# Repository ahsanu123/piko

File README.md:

<h1>🐤 piko </h1>
<p>

</p>

<p align="center">CMSIS DAP Probe</p>

### 🧺 Schematic

## Reference

- make new project Piko, picoprobe based on https://github.com/ErichStyger/mcuoneclipse/tree/master/KiCAD/Projects/PicoLink
- wagiminator ch552 daplink https://github.com/wagiminator/CH552-DAPLink
- yapicoprobe https://github.com/rgrr/yapicoprobe/blob/master/doc/hardware.adoc
- mcu on eclipse picolink https://mcuoneclipse.com/2023/04/08/open-source-picolink-raspberry-pi-rp2040-cmsis-dap-debug-probe/

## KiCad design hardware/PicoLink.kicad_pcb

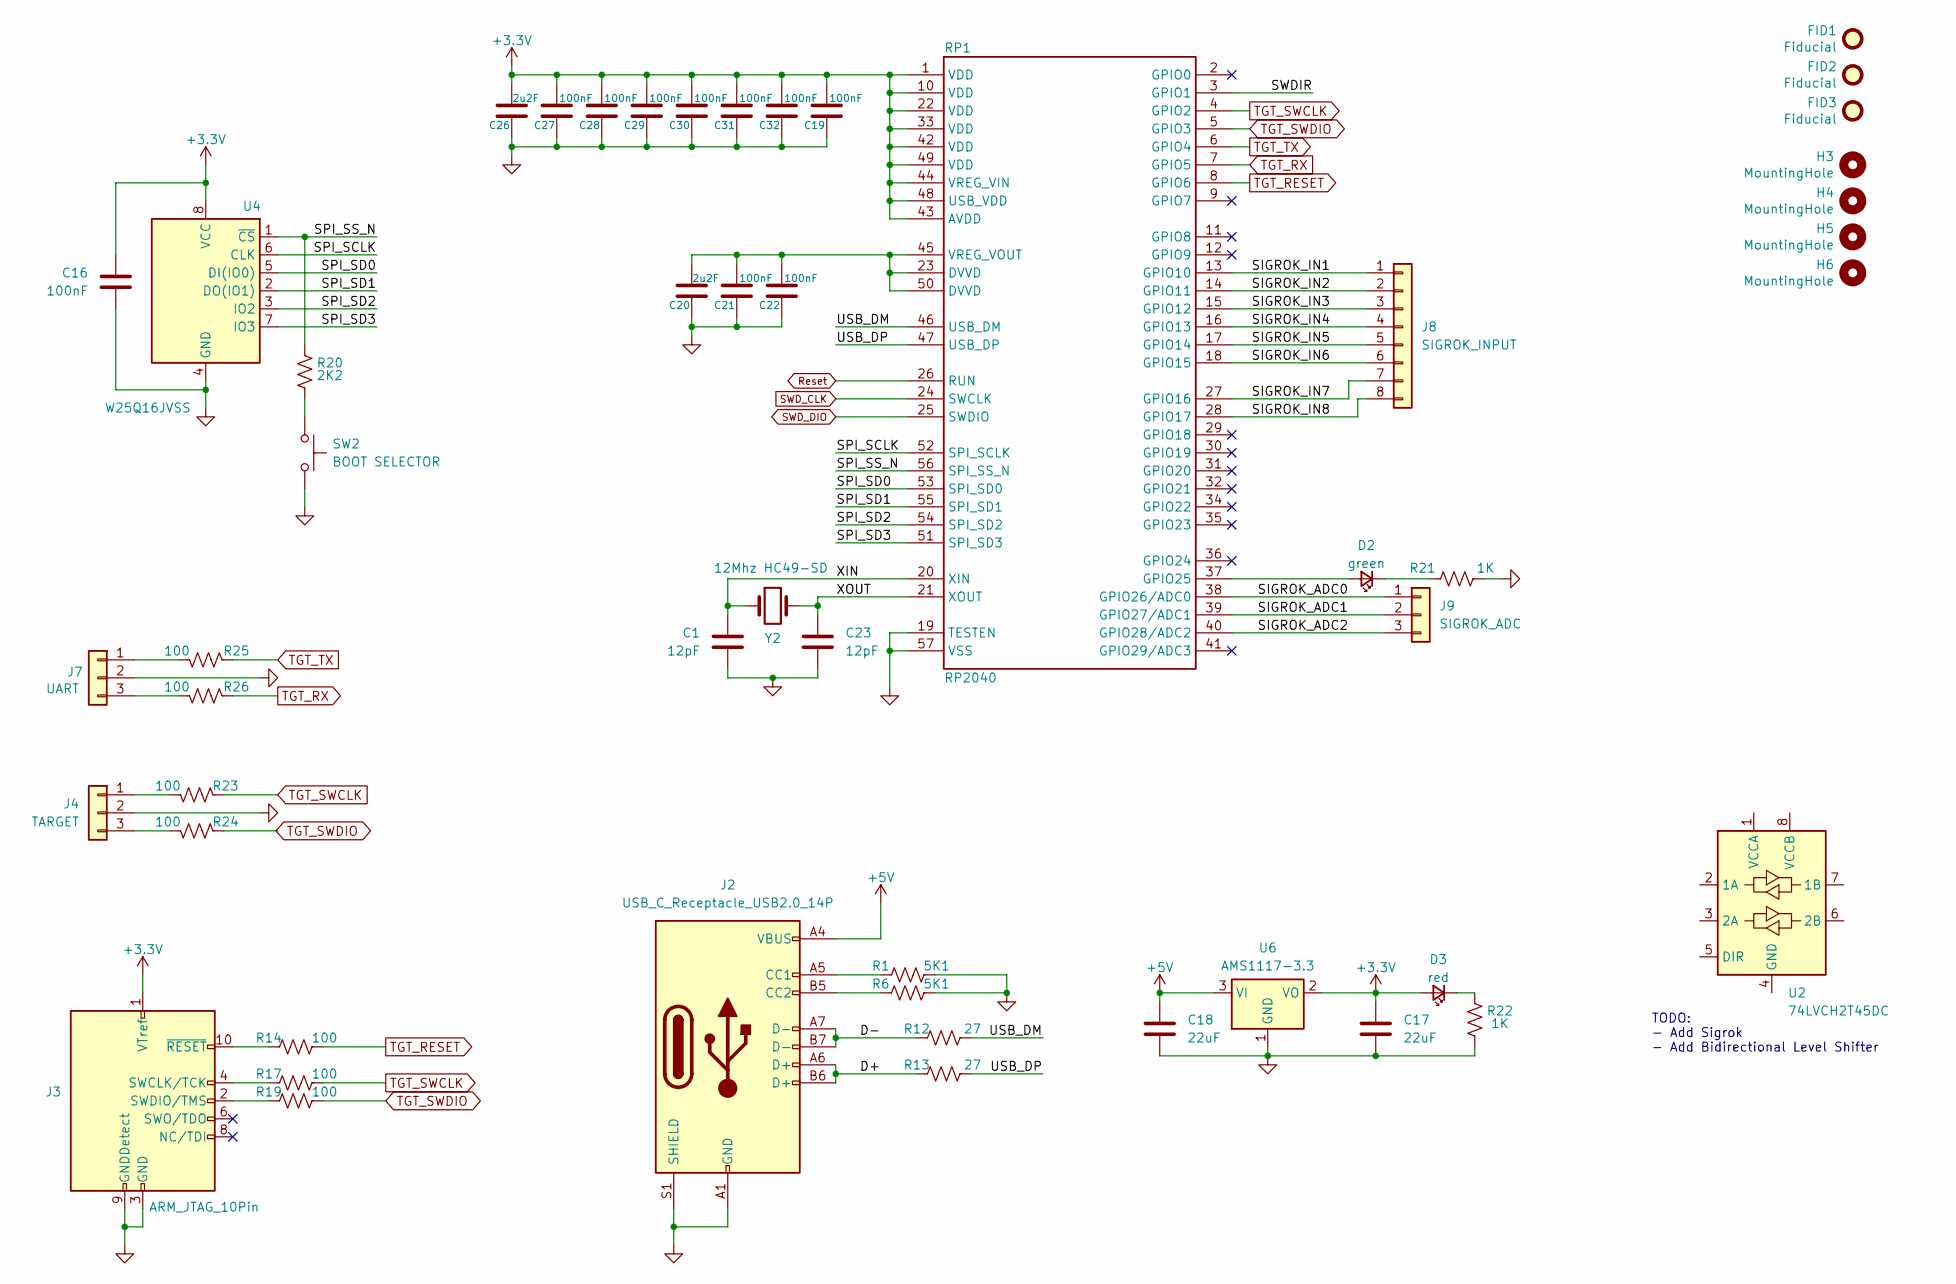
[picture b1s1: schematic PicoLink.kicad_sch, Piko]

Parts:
C1, C23: 12pF; C_0603_1608Metric_Pad1.08x0.95mm_HandSolder
C16, C19, C21, C22, C27, C28, C29, C30, C31, C32: 100nF; C_0603_1608Metric_Pad1.08x0.95mm_HandSolder
C17, C18: 22uF; C_0603_1608Metric_Pad1.08x0.95mm_HandSolder
C20, C26: 2u2F; C_0603_1608Metric_Pad1.08x0.95mm_HandSolder
D2: green; LED_0805_2012Metric_Pad1.15x1.40mm_HandSolder; mouser# 78-VLMTG1300-GS08
D3: red; LED_0805_2012Metric_Pad1.15x1.40mm_HandSolder; mouser# 78-VLMS1300-GS08
FID1, FID2, FID3: Fiducial; Fiducial_1mm_Mask2mm
H3, H4, H5, H6: MountingHole; MountingHole_2.7mm_M2.5
J2: USB_C_Receptacle_USB2.0_14P; USB_C_Receptacle_GCT_USB4110
J3: ARM_JTAG_10Pin; IDC-Header_2x05_P2.54mm_Vertical
J4: TARGET; PinHeader_1x03_P2.54mm_Vertical
J7: UART; PinHeader_1x03_P2.54mm_Vertical
J8: SIGROK_INPUT; PinHeader_1x07_P2.54mm_Vertical
J9: SIGROK_ADC; PinHeader_1x03_P2.54mm_Vertical
R1, R6: 5K1; R_0805_2012Metric_Pad1.20x1.40mm_HandSolder
R12, R13: 27; R_0805_2012Metric_Pad1.20x1.40mm_HandSolder
R14, R17, R19, R23, R24, R25, R26: 100; R_0805_2012Metric_Pad1.20x1.40mm_HandSolder
R20: 2K2; R_0805_2012Metric_Pad1.20x1.40mm_HandSolder
R21, R22: 1K; R_0805_2012Metric_Pad1.20x1.40mm_HandSolder
RP1: RP2040; QFN-56-1EP_7x7mm_P0.4mm_EP3.2x3.2mm; MFR# RPI Chip RP2040-7-500; mouser# 358-RP2040CHIP-7-500
SW2: BOOT SELECTOR; SW_Push_1P1T_NO_6x6mm_H9.5mm
U2: 74LVCH2T45DC; VSSOP-8_2.3x2mm_P0.5mm
U4: W25Q16JVSS; SOIC-8_5.23x5.23mm_P1.27mm
U6: AMS1117-3.3; SOT-223-3_TabPin2
Y2: 12Mhz HC49-SD; Crystal_SMD_HC49-SD_HandSoldering

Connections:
+3.3V: C16.1, C17.1, C19.1, C26.1, C27.1, C28.1, C29.1, C30.1, C31.1, C32.1, D3.2 (A), J3.1 (VTref), RP1.1 (VDD), RP1.10 (VDD), RP1.22 (VDD), RP1.33 (VDD), RP1.42 (VDD), RP1.43 (AVDD), RP1.44 (VREG_VIN), RP1.48 (USB_VDD), RP1.49 (VDD), U4.8 (VCC), U6.2 (VO)
+5V: C18.1, J2.A4 (VBUS), J2.A9 (VBUS), J2.B4 (VBUS), J2.B9 (VBUS), U6.3 (VI)
/D+: J2.A6 (D+), J2.B6 (D+), R13.1
/D-: J2.A7 (D-), J2.B7 (D-), R12.1
/SIGROK_ADC0: J9.1, RP1.38 (GPIO26/ADC0)
/SIGROK_ADC1: J9.2, RP1.39 (GPIO27/ADC1)
/SIGROK_ADC2: J9.3, RP1.40 (GPIO28/ADC2)
/SIGROK_IN1: J8.1, RP1.13 (GPIO10)
/SIGROK_IN2: J8.2, RP1.14 (GPIO11)
/SIGROK_IN3: J8.3, RP1.15 (GPIO12)
/SIGROK_IN4: J8.4, RP1.16 (GPIO13)
/SIGROK_IN5: J8.5, RP1.17 (GPIO14)
/SIGROK_IN6: J8.6, RP1.18 (GPIO15)
/SIGROK_IN7: J8.7, RP1.27 (GPIO16)
/SIGROK_IN8: J8.8, RP1.28 (GPIO17)
/SPI_SCLK: RP1.52 (SPI_SCLK), U4.6 (CLK)
/SPI_SD0: RP1.53 (SPI_SD0), U4.5 (DI(IO0))
/SPI_SD1: RP1.55 (SPI_SD1), U4.2 (DO(IO1))
/SPI_SD2: RP1.54 (SPI_SD2), U4.3 (IO2)
/SPI_SD3: RP1.51 (SPI_SD3), U4.7 (IO3)
/SPI_SS_N: R20.1, RP1.56 (SPI_SS_N), U4.1 (~CS)
/SWDIR: RP1.3 (GPIO1)
/USB_DM: R12.2, RP1.46 (USB_DM)
/USB_DP: R13.2, RP1.47 (USB_DP)
/XIN: C1.1, RP1.20 (XIN), Y2.1
/XOUT: C23.1, RP1.21 (XOUT), Y2.2
GND: C1.2, C16.2, C17.2, C18.2, C19.2, C20.2, C21.2, C22.2, C23.2, C26.2, C27.2, C28.2, C29.2, C30.2, C31.2, C32.2, J2.A1 (GND), J2.A12 (GND), J2.B1 (GND), J2.B12 (GND), J2.S1 (SHIELD), J3.3 (GND), J3.5 (GND), J3.9 (GNDDetect), J4.2, J7.2, R1.2, R6.2, R21.2, R22.2, RP1.19 (TESTEN), RP1.57 (VSS), SW2.2, U4.4 (GND), U6.1 (GND)
unnamed: D2.2 (A), RP1.37 (GPIO25)
unnamed: D2.1 (K), R21.1
unnamed: D3.1 (K), R22.1
unnamed: J2.A5 (CC1), R1.1
unnamed: J2.B5 (CC2), R6.1
unnamed: J3.4 (SWCLK/TCK), R17.1
unnamed: J3.2 (SWDIO/TMS), R19.1
unnamed: J3.10 (~RESET), R14.1
unnamed: J4.1, R23.2
unnamed: J4.3, R24.2
unnamed: J7.1, R25.2
unnamed: J7.3, R26.2
unnamed: R20.2, SW2.1
unnamed: C20.1, C21.1, C22.1, RP1.23 (DVVD), RP1.45 (VREG_VOUT), RP1.50 (DVVD)
Reset: RP1.26 (RUN)
SWD_CLK: RP1.24 (SWCLK)
SWD_DIO: RP1.25 (SWDIO)
TGT_RESET: R14.2, RP1.8 (GPIO6)
TGT_RX: R26.1, RP1.7 (GPIO5)
TGT_SWCLK: R17.2, R23.1, RP1.4 (GPIO2)
TGT_SWDIO: R19.2, R24.1, RP1.5 (GPIO3)
TGT_TX: R25.1, RP1.6 (GPIO4)

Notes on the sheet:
TODO: - Add Sigrok - Add Bidirectional Level Shifter

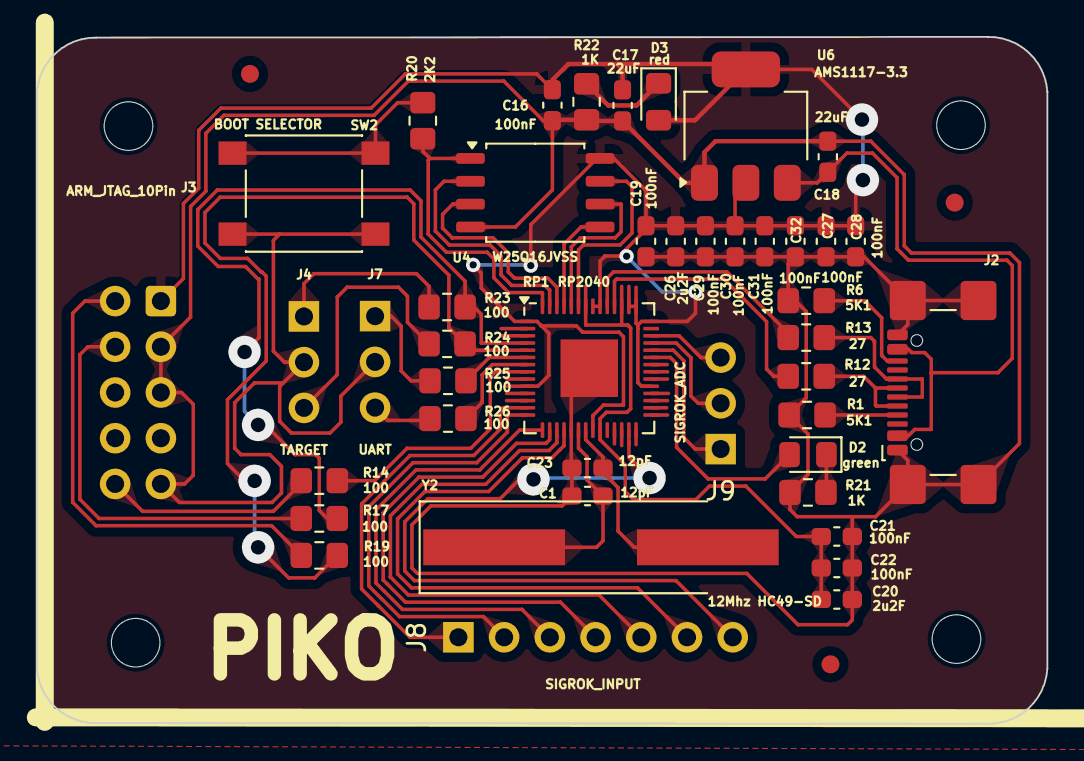
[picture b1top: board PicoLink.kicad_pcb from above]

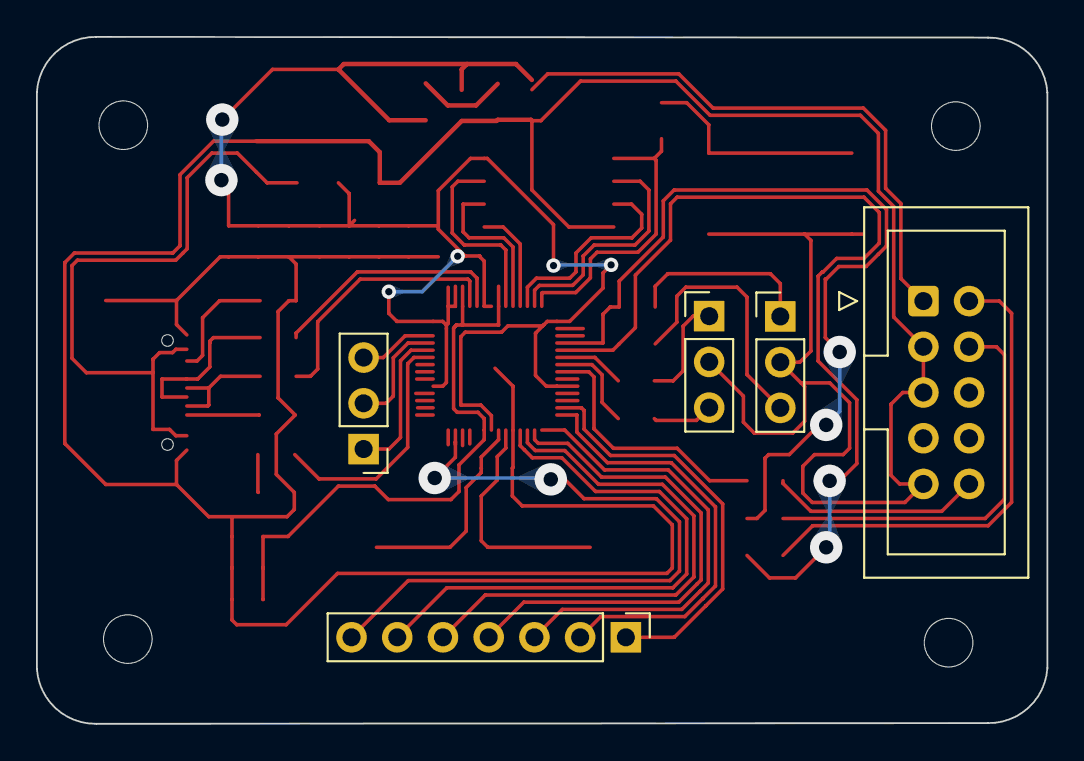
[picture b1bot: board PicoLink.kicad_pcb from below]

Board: 2 copper layers, 56.1 x 38.2 mm, 50 parts (5 on the bottom side), 44 nets.

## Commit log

2025-07-15 [07-15-1901] piko initial commit
    update
2025-07-16 [07-16-1503] small update on schematic
2025-07-16 [07-16-2030] finish rough routing
2025-07-17 [07-17-1304] add edge cut
    Update README.md
2025-07-17 [07-17-1556] update silkscreen
2025-07-17 [07-17-1645] generate gerber files
2025-07-18 [07-18-0738] fabricate pcb
2025-07-18 [07-18-2108] add svg schematic
